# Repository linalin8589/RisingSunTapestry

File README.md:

# RisingSunTapestry
Just lighting a bunch leds when the sun rises. Teehee

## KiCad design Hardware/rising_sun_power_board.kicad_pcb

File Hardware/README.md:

## Power board
Provides power to ESP32 and the neopixels. Takes in 12V

### ECOs 02/28/23
1. Flip the headers for the ESP32 on the layout.

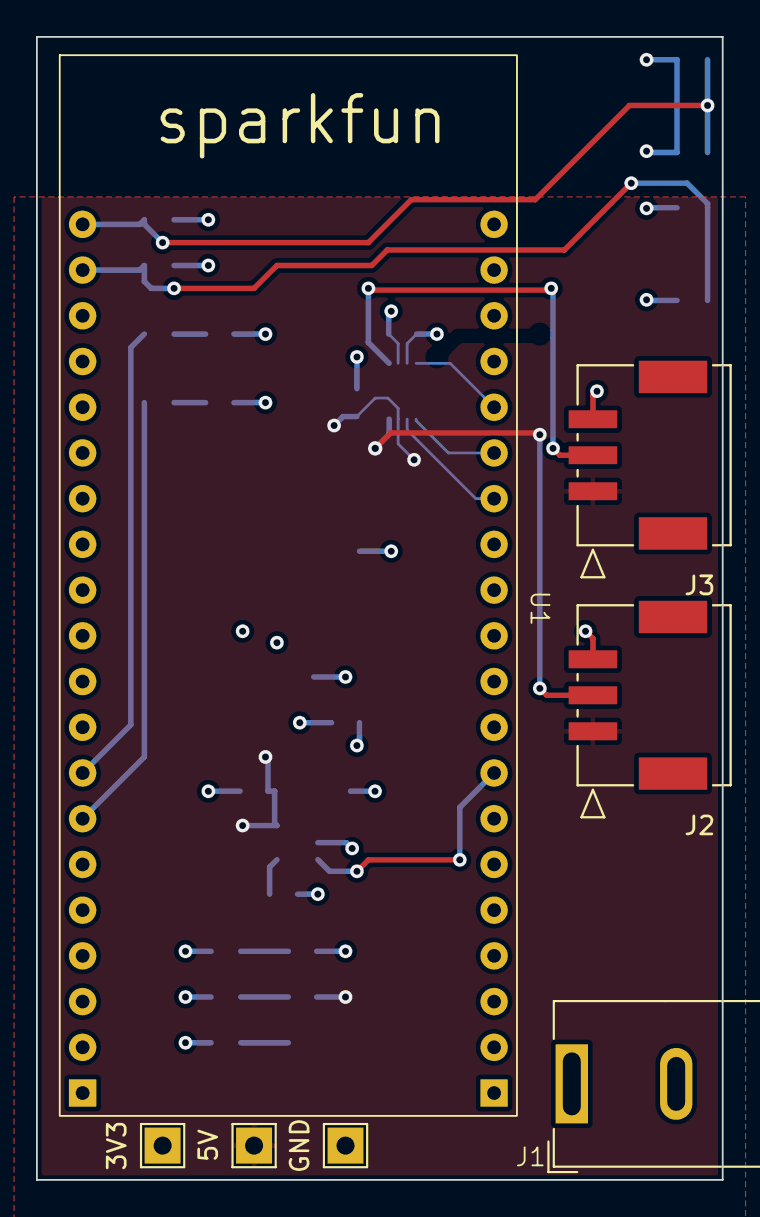
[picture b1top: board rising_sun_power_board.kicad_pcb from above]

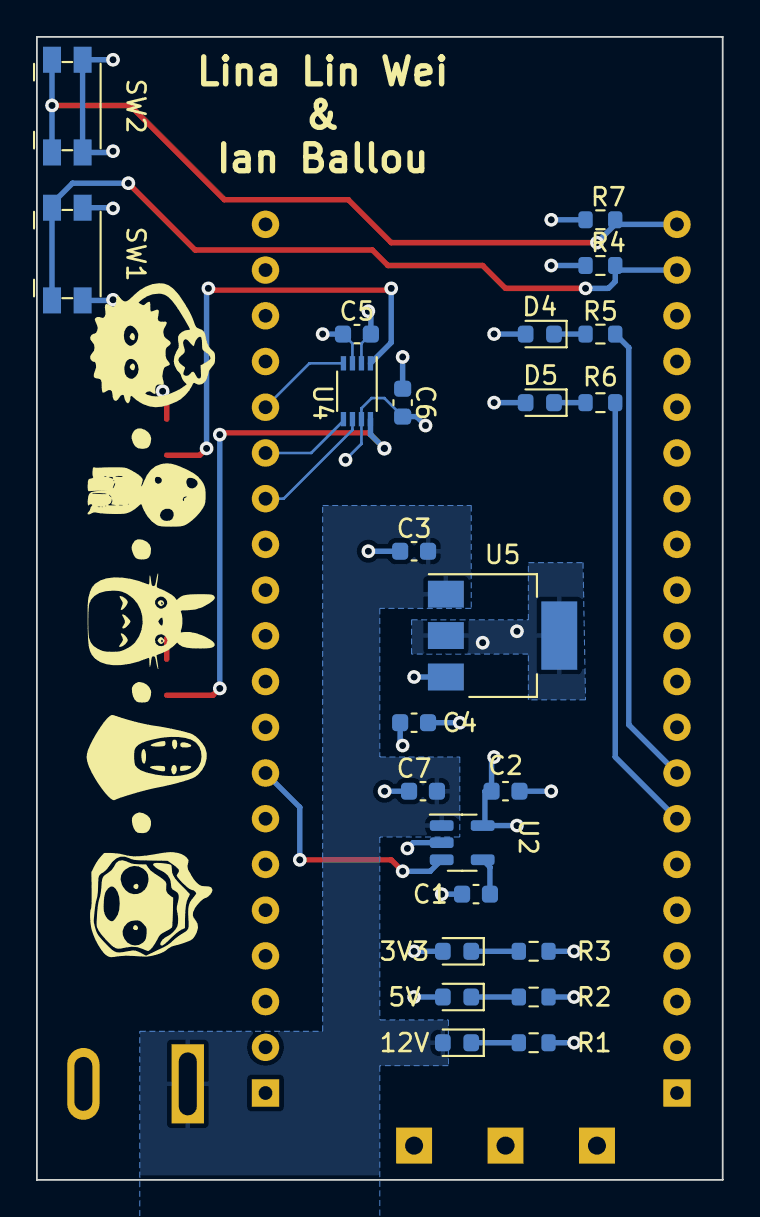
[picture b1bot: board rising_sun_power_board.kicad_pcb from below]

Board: 4 copper layers, 38.1 x 63.5 mm, 31 parts (24 on the bottom side), 20 nets.

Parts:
C1: 470pF; C_0603_1608Metric
C2: 2.2uF; C_0603_1608Metric
C3: 0.33uF; C_0603_1608Metric
C4, C5, C6: 0.1uF; C_0603_1608Metric
C7: 1uF; C_0603_1608Metric
D1: 12V; LED_0603_1608Metric
D2: 5V; LED_0603_1608Metric
D3: 3V3; LED_0603_1608Metric
D4: GPIO1; LED_0603_1608Metric
D5: GPIO2; LED_0603_1608Metric
J1: Barrel_Jack; custom_barrel_jack
J2, J3: Conn_01x03_Socket; CON_5024940370_MOL
R1: 10k; R_0603_1608Metric
R2: 2k; R_0603_1608Metric
R3, R4, R5, R6, R7: 1k; R_0603_1608Metric
SW1, SW2: SW_Push; Panasonic_EVQPUK_EVQPUB
TP1: GND; TestPoint_THTPad_2.0x2.0mm_Drill1.0mm
TP2: 5V; TestPoint_THTPad_2.0x2.0mm_Drill1.0mm
TP3: 3V3; TestPoint_THTPad_2.0x2.0mm_Drill1.0mm
U1: ESP32; ESP32_Thing
U2: MIC5219; SOT-23-5
U4: TXU0102DCUR; VSSOP-8_2.3x2mm_P0.5mm
U5: UA78M33IDCYR; SOT-223

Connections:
+3V3: C4.1, C5.1, D3.2 (A), D4.2 (A), D5.2 (A), R4.1, R7.1, TP3.1, U1.5 (3.3V), U1.25 (3.3V), U4.3 (V_CCA), U5.3 (OUTPUT)
+5V: C2.1, C6.1, D2.2 (A), J2.1, J3.1, TP2.1, U2.5 (V_OUT), U4.7 (V_CCB)
+12V: C3.1, C7.2, D1.2 (A), J1.1, U2.1 (V_IN), U5.1 (INPUT)
/5V_Enable: U1.28 (4), U2.3 (EN)
/GPIO_BUTTON1: R4.2, SW1.1, U1.19 (37)
/GPIO_BUTTON2: R7.2, SW2.1, U1.20 (36)
/GPIO_LED1: R5.2, U1.8 (12)
/GPIO_LED2: R6.2, U1.7 (13)
/LED_ENABLE_3V3_1: U1.35 (19), U4.5 (A1)
/LED_ENABLE_3V3_2: U1.36 (22), U4.4 (A2)
/LED_ENABLE_5V_1: J2.2, U4.8 (B1Y)
/LED_ENABLE_5V_2: J3.2, U4.1 (B2Y)
/LEVEL_SHIFT_EN: U1.34 (23), U4.6 (OE)
GND: C1.2, C2.2, C3.2, C4.2, C5.2, C6.2, C7.1, J1.2, J2.3, J3.3, R1.2, R2.2, R3.2, SW1.2, SW2.2, TP1.1, U1.1 (GND), U1.4 (GND), U1.21 (GND), U1.24 (GND), U1.40 (GND), U2.2 (GND), U4.2 (GND), U5.2 (GND), U5.4 (GND)
unnamed: D1.1 (K), R1.1
unnamed: D2.1 (K), R2.1
unnamed: D3.1 (K), R3.1
unnamed: D4.1 (K), R5.1
unnamed: D5.1 (K), R6.1
unnamed: C1.1, U2.4 (BYP)

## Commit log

2024-02-03 First version. Schematics done
2024-02-03 layout le done
2024-02-03 :octocat: Fixed layout and gpio assignment
2024-02-13 added some digikey part numbers
2024-02-28 Final rev1.0 version
2024-03-06 fixed some gpios connection
